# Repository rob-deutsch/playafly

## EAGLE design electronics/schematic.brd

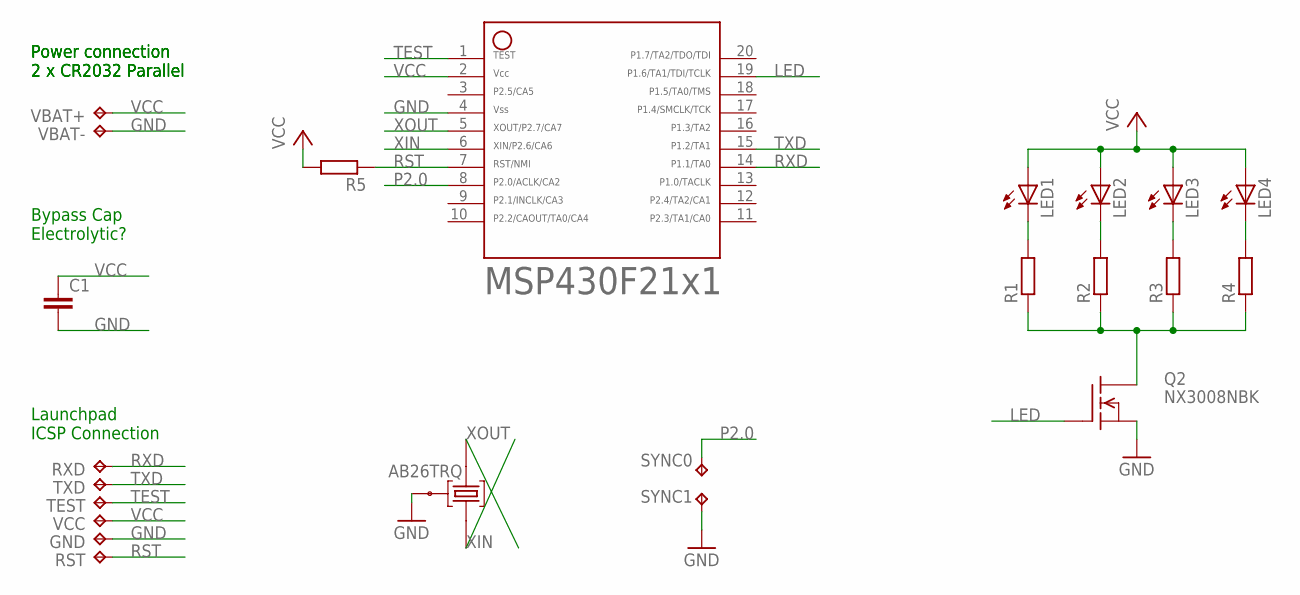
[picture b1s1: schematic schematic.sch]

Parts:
C1: C-EUC0805; C0805
GND: TPTP15R; TP15R
LED1, LED2, LED3, LED4: LEDCHIP-LED0805; CHIP-LED0805
Q2: NX3008NBK; SOT23
R1, R2, R3, R4, R5: R-EU_M0805; M0805
RST: TPTP15R; TP15R
RXD: TPTP15R; TP15R
SYNC0, SYNC1: TPTP15R; TP15R
TEST: TPTP15R; TP15R
TXD: TPTP15R; TP15R
U$1: F21X1---DW20; DW20
U$2: AB26TRQ; QUARZ5
VBAT+: TPTP15R; TP15R
VBAT-: TPTP15R; TP15R
VCC: TPTP15R; TP15R

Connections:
GND: C1.2, GND.TP, Q2.2 (S), SYNC1.TP, U$1.4, U$2.GND@3 (3), VBAT-.TP
LED: Q2.1 (G)
unnamed: LED1.C, R1.2
unnamed: LED2.C, R2.2
unnamed: LED3.C, R3.2
unnamed: LED4.C, R4.2
unnamed: Q2.3 (D), R1.1, R2.1, R3.1, R4.1
P2.0: SYNC0.TP, U$1.8
RST: R5.1, RST.TP, U$1.7
RXD: RXD.TP, U$1.14
TEST: TEST.TP, U$1.1
TXD: TXD.TP, U$1.15
VCC: C1.1, LED1.A, LED2.A, LED3.A, LED4.A, R5.2, U$1.2, VBAT+.TP, VCC.TP
XIN: U$1.6, U$2.P$2 (2)
XOUT: U$1.5, U$2.P$1 (1)

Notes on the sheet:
Power connection 2 x CR2032 Parallel
Bypass Cap Electrolytic?
Launchpad ICSP Connection

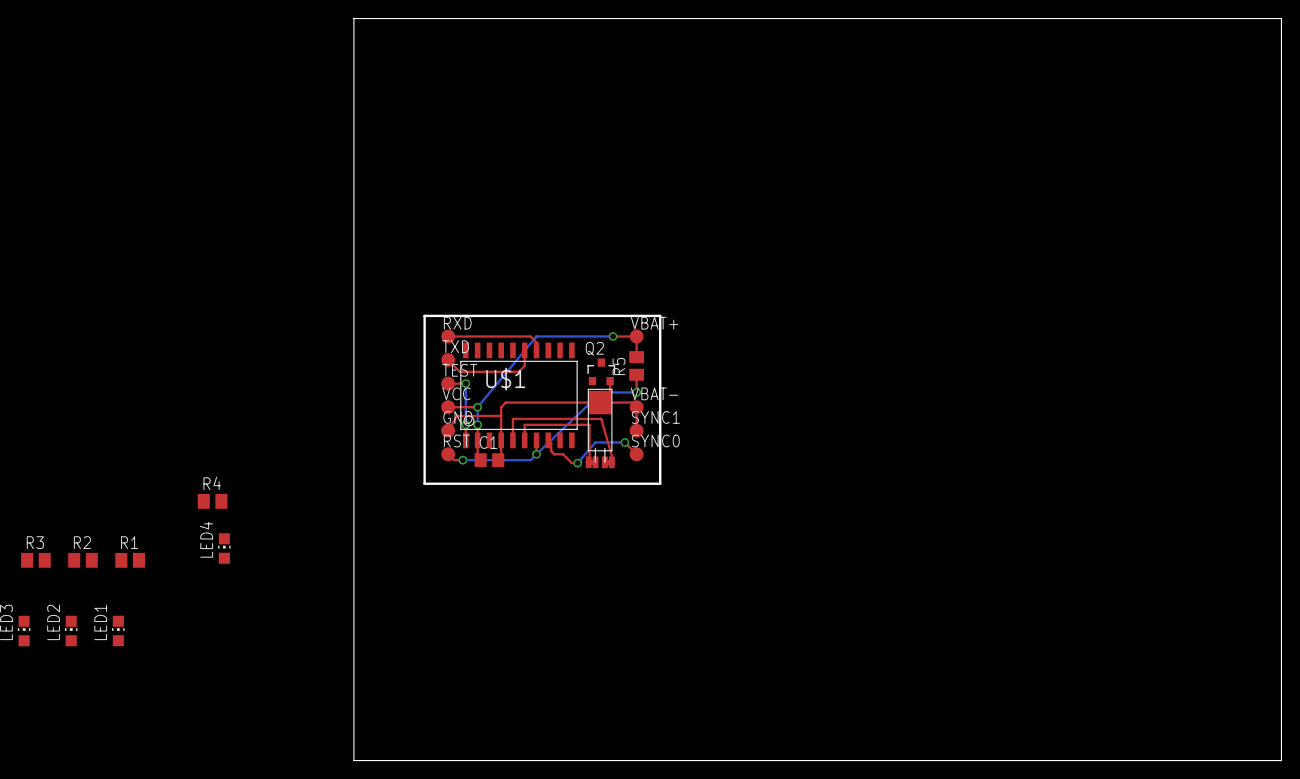
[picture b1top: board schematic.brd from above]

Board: 2 copper layers, 100.0 x 80.0 mm, 23 parts (0 on the bottom side), 14 nets.

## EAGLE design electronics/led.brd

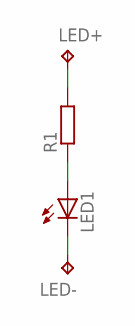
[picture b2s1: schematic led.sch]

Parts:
LED1: LEDCHIPLED_0805; CHIPLED_0805
LED+: TPTP14SQ; TP14SQ
LED-: TPTP14SQ; TP14SQ
R1: R-EU_M0805; M0805

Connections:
unnamed: LED1.A, R1.1
unnamed: LED1.C, LED-.TP
unnamed: LED+.TP, R1.2

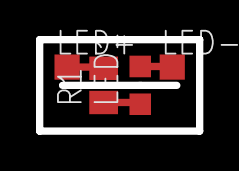
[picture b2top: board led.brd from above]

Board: 2 copper layers, 8.9 x 5.1 mm, 4 parts (0 on the bottom side), 3 nets.

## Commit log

2015-02-07 Initial copy of MSP430-Template
2015-02-07 Basic WDT usage
2015-02-07 WDT+ sourced from ACLK sourced from VLO
2015-02-07 Watchdog source divided by 8192
2015-02-07 In LPM3 sleep mode between flashes
2015-02-08 Checks to see what state it should be in
2015-02-08 Nighttime now has fractional interrupts
2015-02-08 Created pwm.c and associated build to get PWM working
2015-02-08 Got rid of unneeded code
2015-02-08 Attempt to get simple PWM working
2015-02-08 Added documentation
2015-02-08 LED pulsates once per notional second
2015-02-08 LED properly pulsates once per notional second
2015-02-08 Higher PWM frequency makes it smoother
2015-02-08 Fixed Makefile for main.c and finally removed options
2015-02-08 Added PWM pulsating but time not syncronised correctly
2015-02-08 10 seconds off, 10 seconds on, easy
2015-02-08 Pulsates once per second
2015-02-08 Nicer minimum flashing level
2015-02-08 Custom phase progression
2015-02-08 Best flashing so far, exponential curve
2015-02-08 Quick rampup strobe
2015-02-08 CPU should be sleeping during the dya
2015-02-08 Fixed bug that caused LED to flash at 1Hz during the day
2015-02-09 Used _BIS_SR_IRQ so that we don't mangle the stack and interrupt handler
2015-02-10 _BIS_SR_IRQ wasn't freaking overwtiting the SR, only setting certain bits
2015-02-10 Keep WDT firing more often, even in day mode
2015-02-10 Genericised the fraction of a second
2015-02-10 wdttimer not mangling SR any more
2015-02-10 Light strobes in and out
2015-02-10 Reset button now syncs the clock
2015-02-10 Fixed NMI interrupt to ensure that it allowed NMI again. Removed code turning P1 BIT) on.
2015-02-10 May as well turn off all LPM bits before setting new LPM
2015-02-10 Added propert rounding to sync interrupt
2015-02-11 Unix time input from Makefile
2015-02-11 Cleaned up timestamp and debug code a bit
2015-02-12 Debug binary ends in _debug.elf
2015-02-12 Enough code change to get to 750 bytes
2015-02-12 Maths operations can be made smaller
2015-02-12 Fixed bug in reset routins
2015-02-12 Small space saving for unix_time_crac
2015-02-14 Now operating on frequency of 32khz
2015-02-14 testing code
2015-02-14 Added hardware design files
2015-02-22 Original acrylic files, and derivations created
2015-04-12 Moved to cuts to seperate layer
2015-04-12 Fixed up colours for etch
2015-04-27 Added documentation and schematic
2015-04-27 Added abracon library
2015-05-24 Board getting close. Before switching Around
2015-05-24 Finished 1 layer design
2015-05-24 Finished two layer design
2015-05-24 Added bypass capacitor
2015-05-24 Very nice and finished
2015-05-24 Small adjustments
2015-05-24 Rotated FET
2015-05-24 Initial LED board
2015-05-31 RC0. Actual MOSTFET. Added sync pulse. Included LEDs
2015-05-31 Timer_A PWM clock divided by 8 and TAR reset before changing PWM
2015-05-31 new board design
2015-05-31 Moved cap closer to micro
2015-08-16 Final acrylic design
